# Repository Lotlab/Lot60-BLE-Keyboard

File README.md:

# Lot60-BLE Keyboard hardware

A 60% BLE/USB keyboard. License: CC-BY-SA

PLEASE REMOVE MY LOGO BEFORE SELLING THIS KEYBOARD.

## Rev A/B

Using nRF51822 as the main controller, CH554 as the USB chip.

Firmware see: [lotlab/nrf51822-keyboard](https://github.com/Lotlab/nrf51822-keyboard).

## Rev C/D/E/F

Using nRF52810 as the main controller, CH554 as the USB chip.

Firmware see:  [lotlab/nrf52-keyboard](https://github.com/Lotlab/nrf52-keyboard)

## Changelog:

### Rev B

- Fix broken ADC check pin.
- Fix ch554 powered by battery problem.

### Rev C

- Replace nRF51822 with nRF52810
- Replace USB micro with USB Type-C
- Add RGB LED.

### Rev D

- Remove UART test point.
- Change keyboard logo.
- Rework USB circuit.

### Rev E

- Rename MOSI and CLK to UART_TX and UART_RX
- Remove UART check pin.
- Swap GPIO0 and GPIO2 on the bottom jacket.
- Swap pin for GPIO2 and Caps LED.
- Add reset button for nRF52810. (Reuse with GPIO2)

### Rev F

- Add usb-powered only support.

# Lot60-BLE 键盘硬件

一个60%的蓝牙USB双模开源键盘，授权协议：CC-BY-SA。

此键盘fork自GH60，沿用GH60的键盘孔位和阵列线路。

请不要直接使用此库制作硬件并售卖。若需要售卖，请至少做出一些改动并删除LOGO。

## 版本 A/B

使用nRF51822作为键盘主控，CH552/4作为USB控制器。

键盘固件: [lotlab/nrf51822-keyboard](https://github.com/Lotlab/nrf51822-keyboard).

## 版本 C/D/E/F

使用nRF52810作为键盘主控，CH552/4作为USB控制器。

键盘固件:  [lotlab/nrf52-keyboard](https://github.com/Lotlab/nrf52-keyboard)

## 更新日志

### Rev B

- 修正电量检测ADC pin不正确的问题
- 修正CH554受到电池供电而在没有USB接入下工作的问题。

### Rev C

- 替换主控为nRF52810
- 使用Type-C接口
- 添加RGB指示灯

### Rev D

- 删除UART的测试点
- 更改键盘Logo
- 修改USB部分的线路
- 将USB下载按钮修改为正常的按钮

### Rev E

- 将MOSI和CLK重命名为UART_TX和UART_RX，并移除MISO(UART检测)PIN
- 交换了键盘底部GPIO0和GPIO2的次序
- 交换了GPIO2和大写锁定灯的硬件PIN
- 为nRF52810增加了Reset按钮（与GPIO2共用）

### Rev F

- 增加了双电源供电

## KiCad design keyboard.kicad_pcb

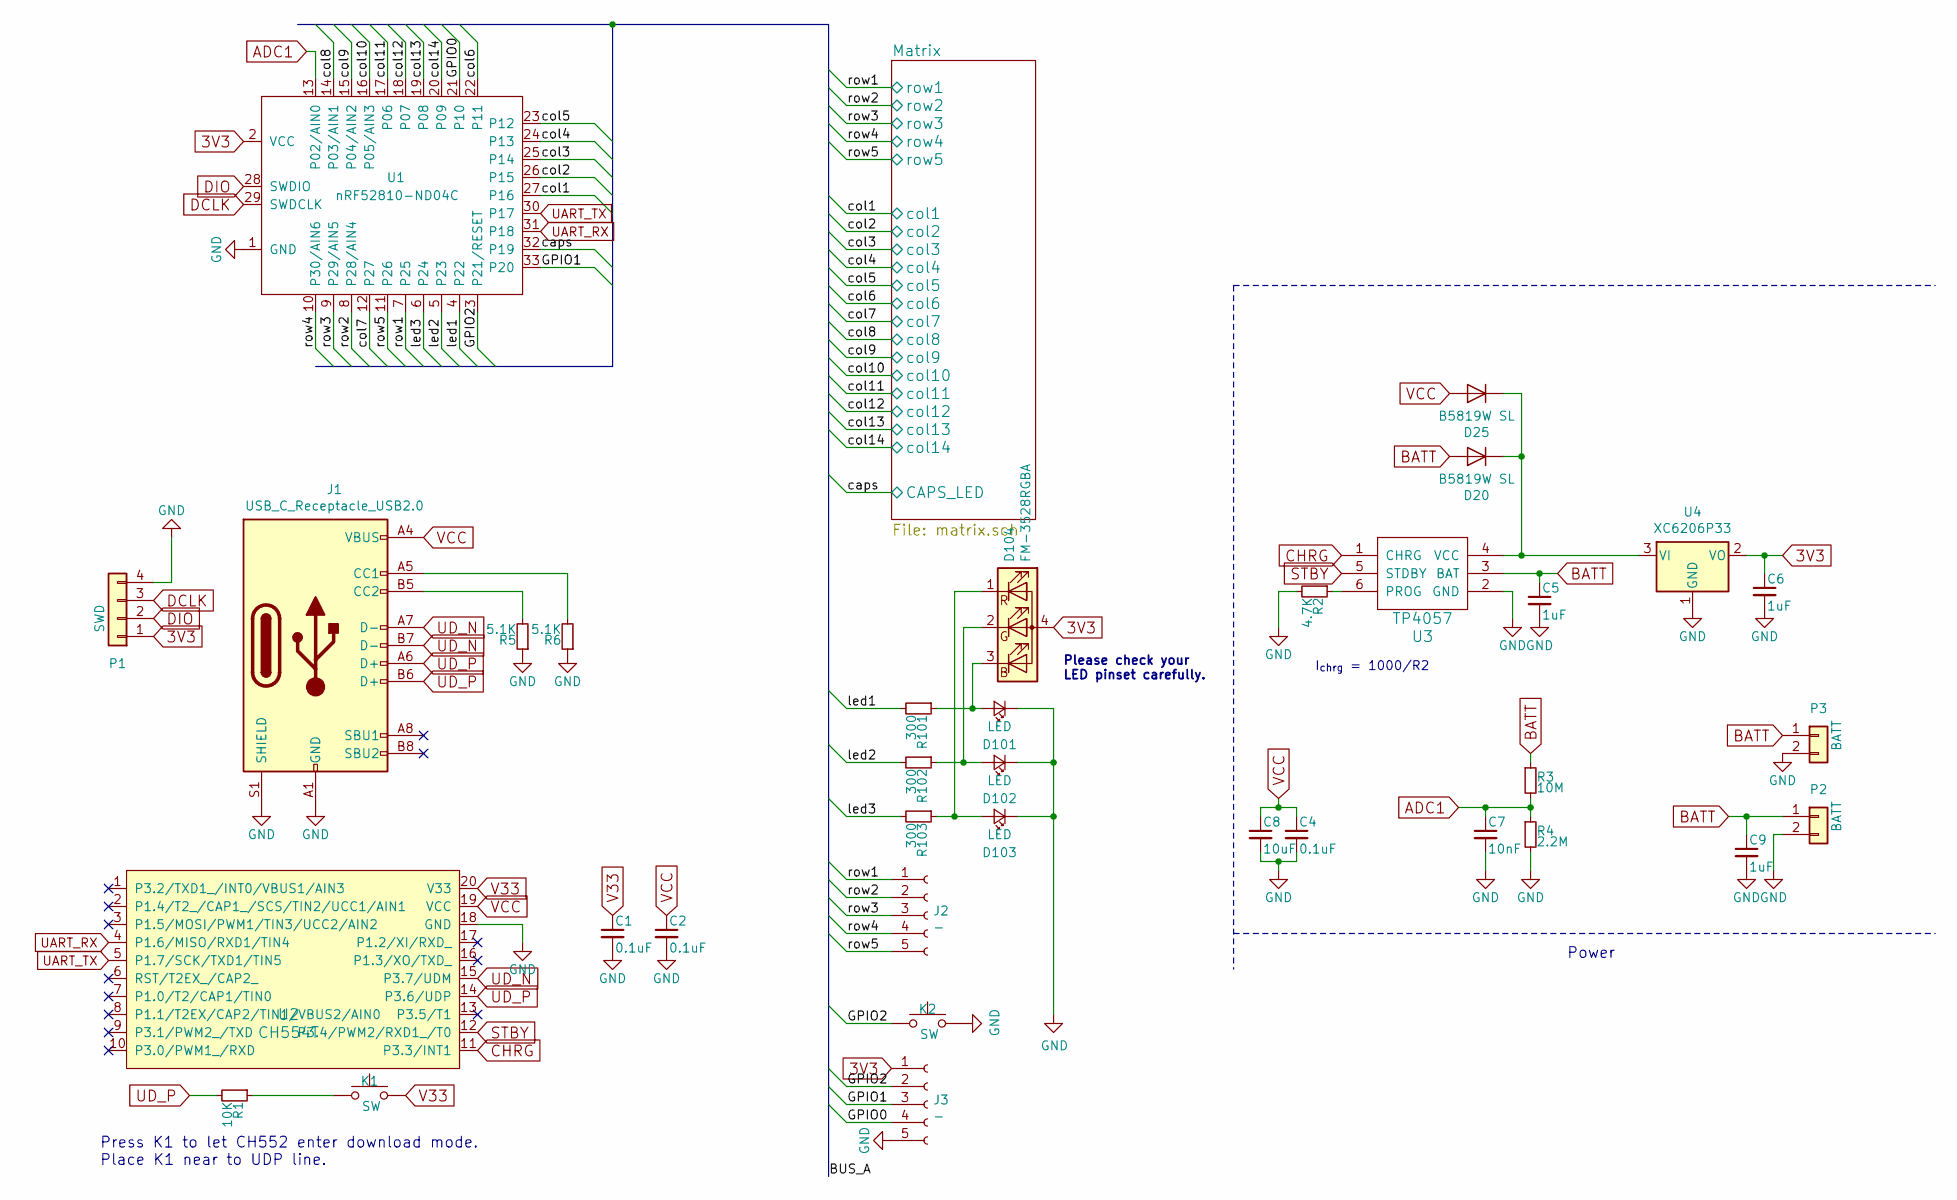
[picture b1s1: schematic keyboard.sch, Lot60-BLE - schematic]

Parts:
C1, C2, C4: 0.1uF; C_0805_2012Metric
C5, C6, C9: 1uF; C_0805_2012Metric
C7: 10nF; C_0805_2012Metric
C8: 10uF; C_0805_2012Metric
D20, D25: B5819W SL; D_SOD-123
D101, D102, D103: LED; MX1A-led
D104: FM-3528RGBA; LED_RGB_1210
J1: USB_C_Receptacle_USB2.0; USB_C_SIMPLE
J2, J3: -; PinSocket_1x05_P2.54mm_Vertical
K1, K2: SW; SW_SPST_TL3342
P1: SWD; PinSocket_1x04_P2.54mm_Vertical
P2: BATT; PinHeader_1x02_P2.54mm_Vertical
P3: BATT; PinSocket_1x02_P2.00mm_Vertical
R1: 10K; R_0805_2012Metric
R2: 4.7K; R_0805_2012Metric
R3: 10M; R_0805_2012Metric
R4: 2.2M; R_0805_2012Metric
R5, R6: 5.1K; R_0805_2012Metric
R101, R102, R103: 300; R_0805_2012Metric
U1: nRF52810-ND04C
U2: CH554T; SSOP-20_4.4x6.5mm_P0.65mm
U3: TP4057; SOT-23-6
U4: XC6206P33; SOT-23

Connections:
3V3: C6.1, D104.4 (A), J3.1, P1.1, U1.2 (VCC), U4.2 (VO)
/GPIO0: J3.4, U1.21 (P10)
/GPIO1: J3.3, U1.33 (P20)
/GPIO2: J3.2, K2.1, U1.3 (P21/RESET)
/caps: U1.32 (P19); also elsewhere on the board
/col1: U1.27 (P16); also elsewhere on the board
/col2: U1.26 (P15); also elsewhere on the board
/col3: U1.25 (P14); also elsewhere on the board
/col4: U1.24 (P13); also elsewhere on the board
/col5: U1.23 (P12); also elsewhere on the board
/col6: U1.22 (P11); also elsewhere on the board
/col7: U1.12 (P27); also elsewhere on the board
/col8: U1.14 (P03/AIN1); also elsewhere on the board
/col9: U1.15 (P04/AIN2); also elsewhere on the board
/col10: U1.16 (P05/AIN3); also elsewhere on the board
/col11: U1.17 (P06); also elsewhere on the board
/col12: U1.18 (P07); also elsewhere on the board
/col13: U1.19 (P08); also elsewhere on the board
/col14: U1.20 (P09); also elsewhere on the board
/led1: R101.2, U1.4 (P22)
/led2: R102.2, U1.5 (P23)
/led3: R103.2, U1.6 (P24)
/row1: J2.1, U1.7 (P25); also elsewhere on the board
/row2: J2.2, U1.8 (P28/AIN4); also elsewhere on the board
/row3: J2.3, U1.9 (P29/AIN5); also elsewhere on the board
/row4: J2.4, U1.10 (P30/AIN6); also elsewhere on the board
/row5: J2.5, U1.11 (P26); also elsewhere on the board
ADC1: C7.1, R3.2, R4.1, U1.13 (P02/AIN0)
BATT: C5.1, C9.1, D20.2 (A), P2.1, P3.1, R3.1, U3.3 (BAT)
CHRG: U2.11 (P3.3/INT1), U3.1 (CHRG)
DCLK: P1.3, U1.29 (SWDCLK)
DIO: P1.2, U1.28 (SWDIO)
GND: C1.2, C2.2, C4.2, C5.2, C6.2, C7.2, C8.2, C9.2, D101.1 (K), D102.1 (K), D103.1 (K), J1.A1 (GND), J1.A12 (GND), J1.B1 (GND), J1.B12 (GND), J1.S1 (SHIELD), J3.5, K2.2, P1.4, P2.2, P3.2, R2.2, R4.2, R5.1, R6.1, U1.1 (GND), U2.18 (GND), U3.2 (GND), U4.1 (GND); also elsewhere on the board
unnamed: D20.1 (K), D25.1 (K), U3.4 (VCC), U4.3 (VI)
unnamed: D101.2 (A), D104.3 (BK), R101.1
unnamed: D102.2 (A), D104.2 (GK), R102.1
unnamed: D103.2 (A), D104.1 (RK), R103.1
unnamed: J1.A5 (CC1), R6.2
unnamed: J1.B5 (CC2), R5.2
unnamed: K1.1, R1.1
unnamed: R2.1, U3.6 (PROG)
STBY: U2.12 (P3.4/PWM2/RXD1_/T0), U3.5 (STDBY)
UART_RX: U1.31 (P18), U2.4 (P1.6/MISO/RXD1/TIN4)
UART_TX: U1.30 (P17), U2.5 (P1.7/SCK/TXD1/TIN5)
UD_N: J1.A7 (D-), J1.B7 (D-), U2.15 (P3.7/UDM)
UD_P: J1.A6 (D+), J1.B6 (D+), R1.2, U2.14 (P3.6/UDP)
V33: C1.1, K1.2, U2.20 (V33)
VCC: C2.1, C4.1, C8.1, D25.2 (A), J1.A4 (VBUS), J1.A9 (VBUS), J1.B4 (VBUS), J1.B9 (VBUS), U2.19 (VCC)

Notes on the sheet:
Power
Press K1 to let CH552 enter download mode. Place K1 near to UDP line.
I_{chrg} = 1000/R2
Please check your LED pinset carefully.

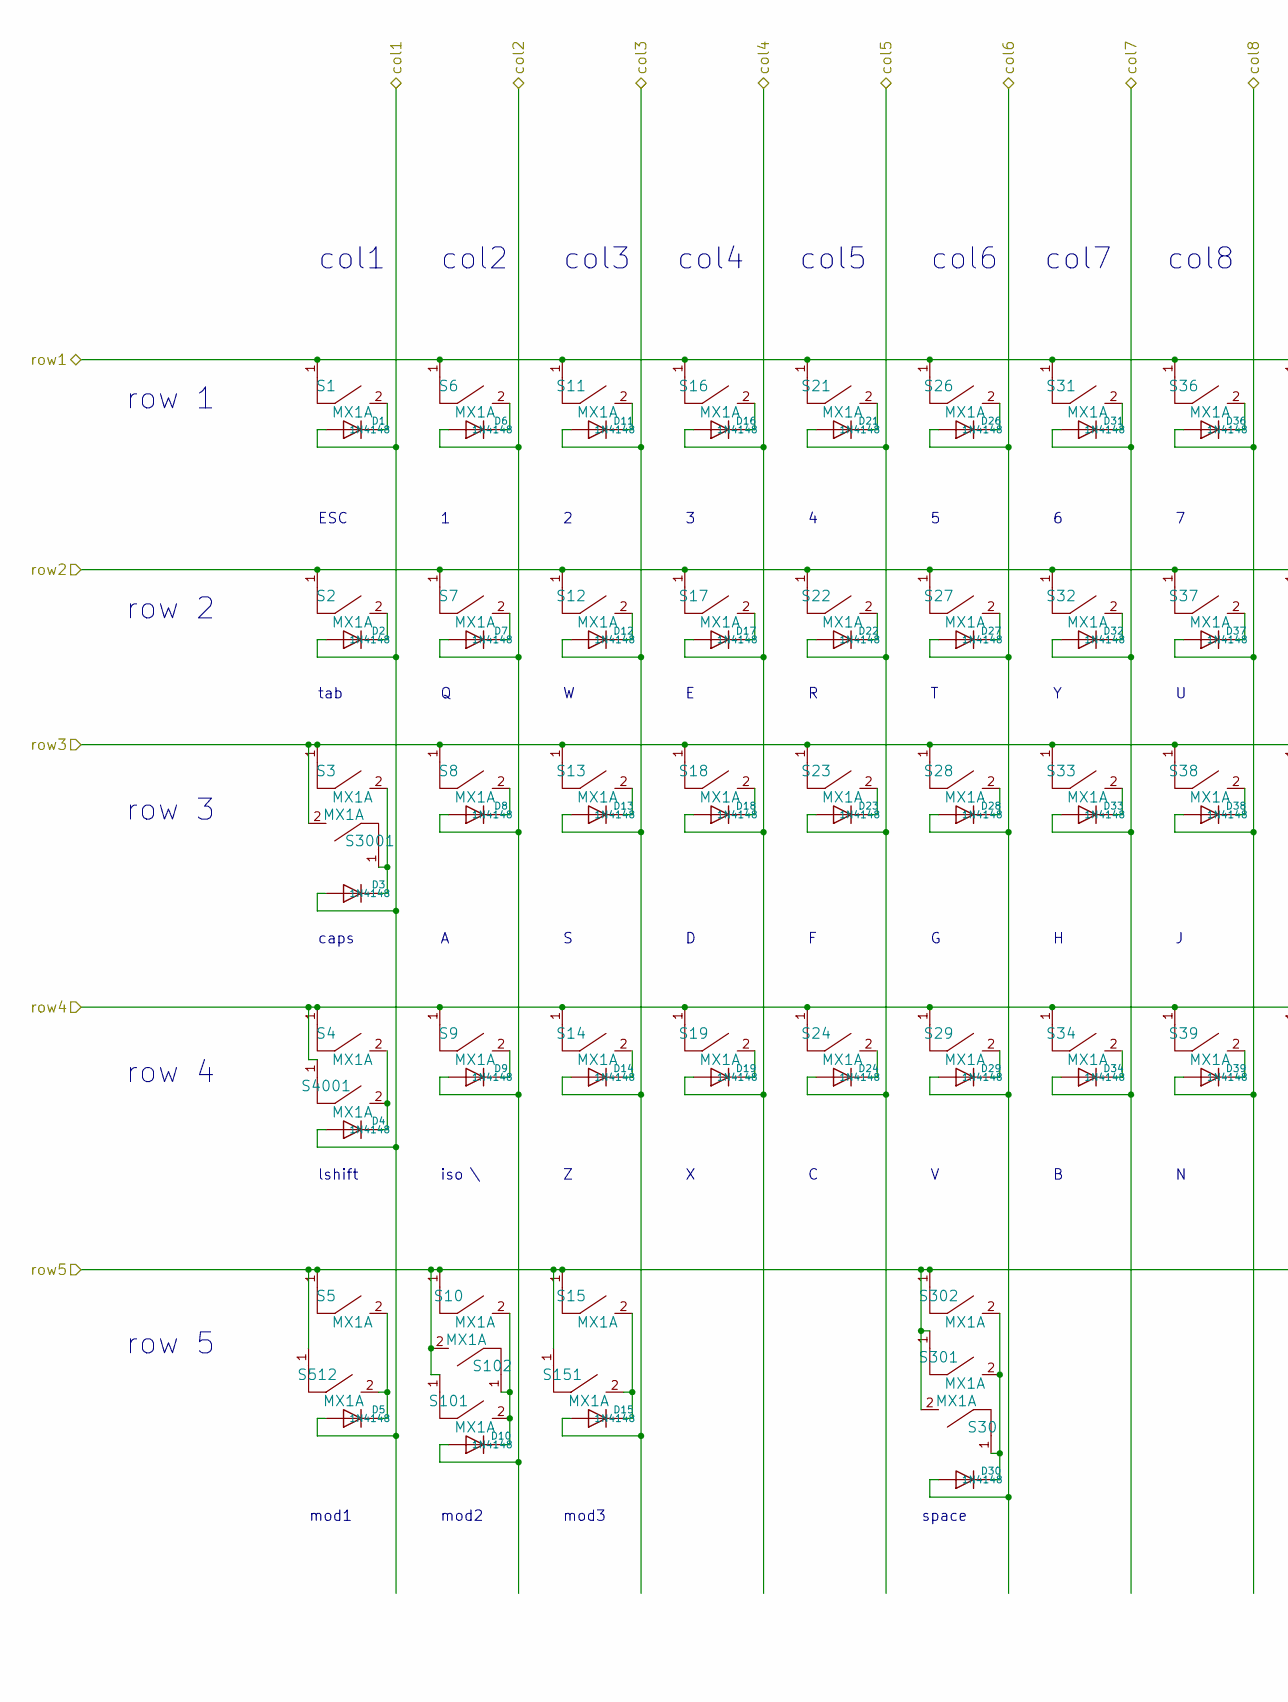
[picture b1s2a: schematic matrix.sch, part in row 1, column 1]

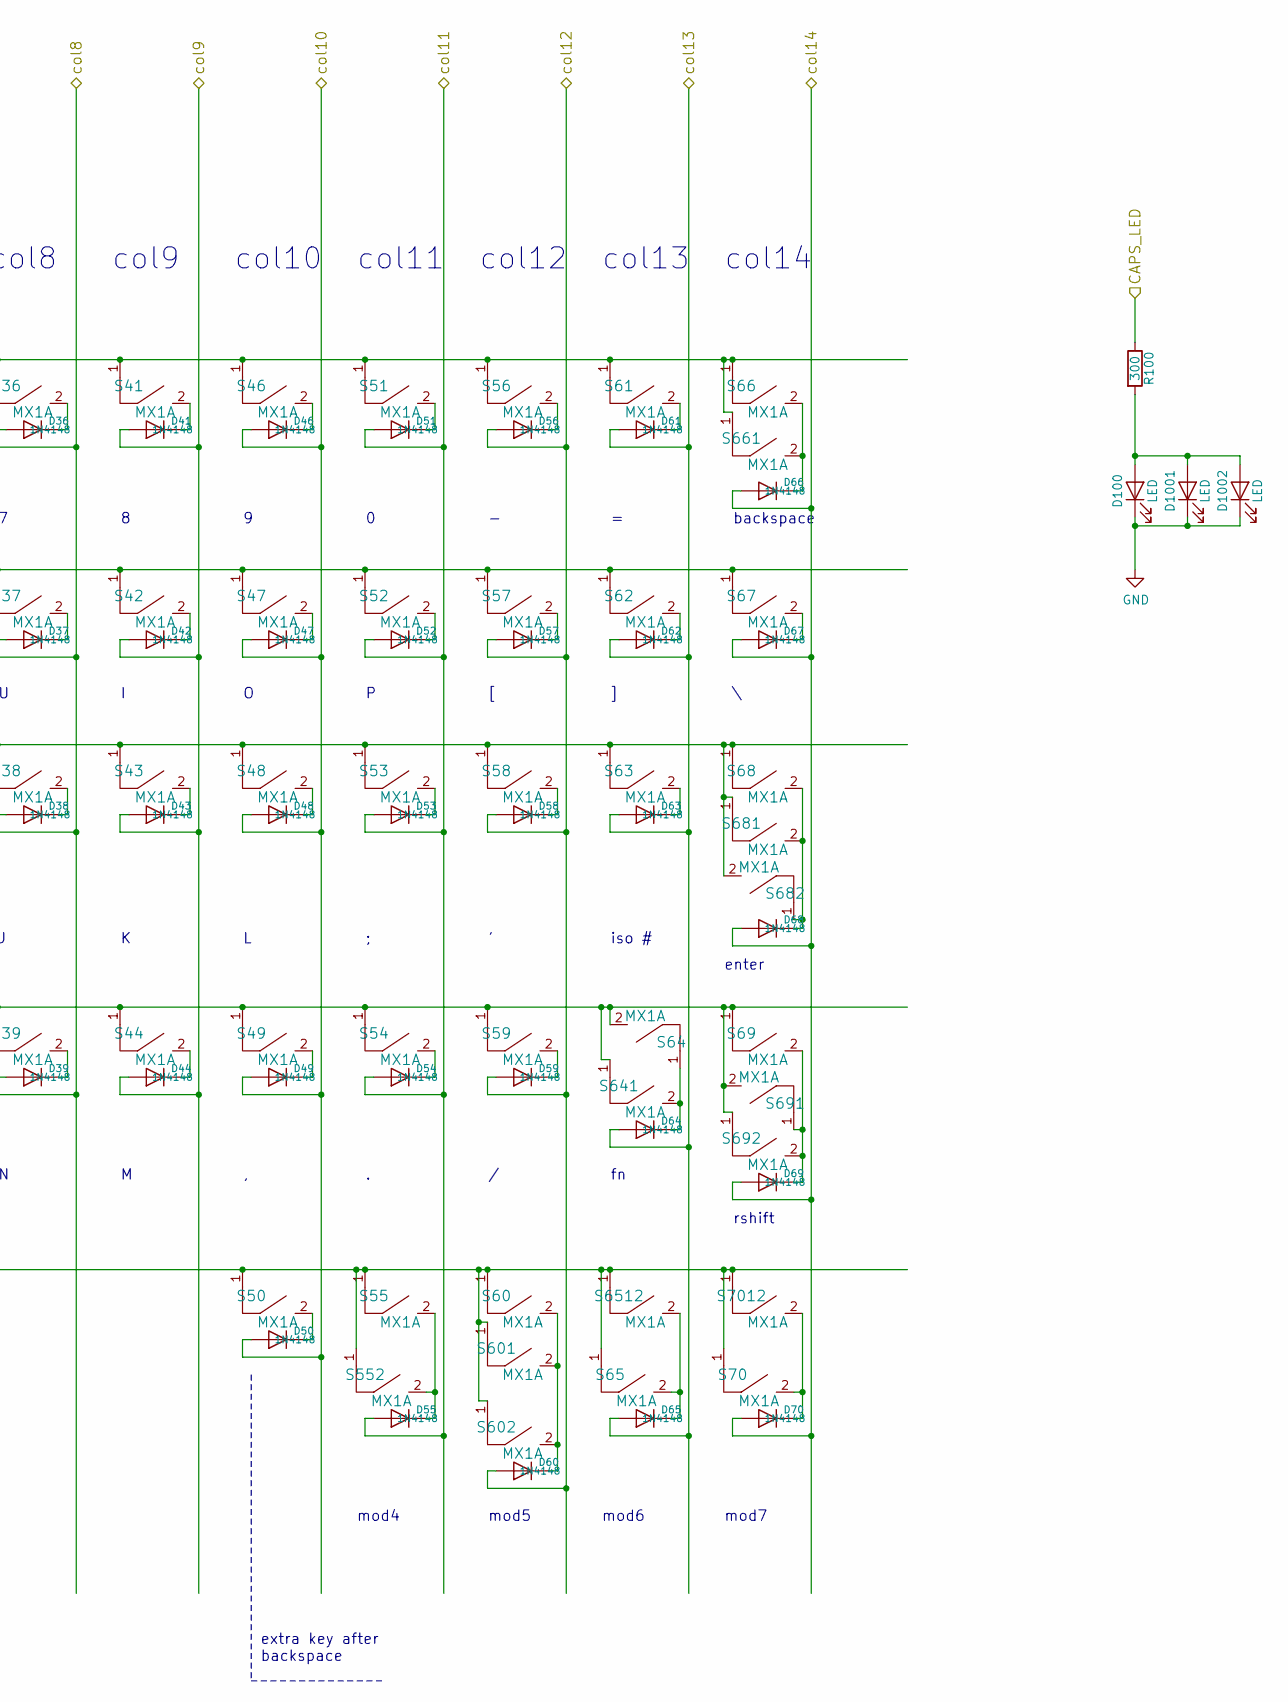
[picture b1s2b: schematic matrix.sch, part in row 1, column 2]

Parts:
D1, D2, D3, D4, D5, D6, D7, D8, D9, D10, D11, D12, D13, D14, D15, D16, D17, D18, D19, D21, D22, D23, D24, D26, D27, D28, D29, D30, D31, D32, D33, D34, D36, D37, D38, D39, D41, D42, D43, D44, D46, D47, D48, D49, D50, D51, D52, D53, D54, D55, D56, D57, D58, D59, D60, D61, D62, D63, D64, D65, D66, D67, D68, D69, D70: 1N4148; D_0805_2012Metric
D100, D1001, D1002: LED; MX1A-led
R100: 300; R_0805_2012Metric
S1, S2, S3, S4, S5, S6, S7, S8, S9, S10, S11, S12, S13, S14, S15, S16, S17, S18, S19, S21, S22, S23, S24, S26, S27, S28, S29, S30, S31, S32, S33, S34, S36, S37, S38, S39, S41, S42, S43, S44, S46, S47, S48, S49, S50, S51, S52, S53, S54, S55, S56, S57, S58, S59, S60, S61, S62, S63, S64, S65, S66, S67, S68, S69, S70, S101, S102, S151, S301, S302, S512, S552, S601, S602, S641, S661, S681, S682, S691, S692, S3001, S4001, S6512, S7012: MX1A; MX1A-simple

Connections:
/caps: R100.1; also elsewhere on the board
/col1: D1.2 (A), D2.2 (A), D3.2 (A), D4.2 (A), D5.2 (A); also elsewhere on the board
/col2: D6.2 (A), D7.2 (A), D8.2 (A), D9.2 (A), D10.2 (A); also elsewhere on the board
/col3: D11.2 (A), D12.2 (A), D13.2 (A), D14.2 (A), D15.2 (A); also elsewhere on the board
/col4: D16.2 (A), D17.2 (A), D18.2 (A), D19.2 (A); also elsewhere on the board
/col5: D21.2 (A), D22.2 (A), D23.2 (A), D24.2 (A); also elsewhere on the board
/col6: D26.2 (A), D27.2 (A), D28.2 (A), D29.2 (A), D30.2 (A); also elsewhere on the board
/col7: D31.2 (A), D32.2 (A), D33.2 (A), D34.2 (A); also elsewhere on the board
/col8: D36.2 (A), D37.2 (A), D38.2 (A), D39.2 (A); also elsewhere on the board
/col9: D41.2 (A), D42.2 (A), D43.2 (A), D44.2 (A); also elsewhere on the board
/col10: D46.2 (A), D47.2 (A), D48.2 (A), D49.2 (A), D50.2 (A); also elsewhere on the board
/col11: D51.2 (A), D52.2 (A), D53.2 (A), D54.2 (A), D55.2 (A); also elsewhere on the board
/col12: D56.2 (A), D57.2 (A), D58.2 (A), D59.2 (A), D60.2 (A); also elsewhere on the board
/col13: D61.2 (A), D62.2 (A), D63.2 (A), D64.2 (A), D65.2 (A); also elsewhere on the board
/col14: D66.2 (A), D67.2 (A), D68.2 (A), D69.2 (A), D70.2 (A); also elsewhere on the board
/row1: S1.1, S6.1, S11.1, S16.1, S21.1, S26.1, S31.1, S36.1, S41.1, S46.1, S51.1, S56.1, S61.1, S66.1, S661.1; also elsewhere on the board
/row2: S2.1, S7.1, S12.1, S17.1, S22.1, S27.1, S32.1, S37.1, S42.1, S47.1, S52.1, S57.1, S62.1, S67.1; also elsewhere on the board
/row3: S3.1, S8.1, S13.1, S18.1, S23.1, S28.1, S33.1, S38.1, S43.1, S48.1, S53.1, S58.1, S63.1, S68.1, S681.1, S682.2, S3001.2; also elsewhere on the board
/row4: S4.1, S9.1, S14.1, S19.1, S24.1, S29.1, S34.1, S39.1, S44.1, S49.1, S54.1, S59.1, S64.2, S69.1, S641.1, S691.2, S692.1, S4001.1; also elsewhere on the board
/row5: S5.1, S10.1, S15.1, S30.2, S50.1, S55.1, S60.1, S65.1, S70.1, S101.1, S102.2, S151.1, S301.1, S302.1, S512.1, S552.1, S601.1, S602.1, S6512.1, S7012.1; also elsewhere on the board
GND: D100.1 (K), D1001.1 (K), D1002.1 (K); also elsewhere on the board
unnamed: D1.1 (K), S1.2
unnamed: D2.1 (K), S2.2
unnamed: D3.1 (K), S3.2, S3001.1
unnamed: D4.1 (K), S4.2, S4001.2
unnamed: D5.1 (K), S5.2, S512.2
unnamed: D6.1 (K), S6.2
unnamed: D7.1 (K), S7.2
unnamed: D8.1 (K), S8.2
unnamed: D9.1 (K), S9.2
unnamed: D10.1 (K), S10.2, S101.2, S102.1
unnamed: D11.1 (K), S11.2
unnamed: D12.1 (K), S12.2
unnamed: D13.1 (K), S13.2
unnamed: D14.1 (K), S14.2
unnamed: D15.1 (K), S15.2, S151.2
unnamed: D16.1 (K), S16.2
unnamed: D17.1 (K), S17.2
unnamed: D18.1 (K), S18.2
unnamed: D19.1 (K), S19.2
unnamed: D21.1 (K), S21.2
unnamed: D22.1 (K), S22.2
unnamed: D23.1 (K), S23.2
unnamed: D24.1 (K), S24.2
unnamed: D26.1 (K), S26.2
unnamed: D27.1 (K), S27.2
unnamed: D28.1 (K), S28.2
unnamed: D29.1 (K), S29.2
unnamed: D30.1 (K), S30.1, S301.2, S302.2
unnamed: D31.1 (K), S31.2
unnamed: D32.1 (K), S32.2
unnamed: D33.1 (K), S33.2
unnamed: D34.1 (K), S34.2
unnamed: D36.1 (K), S36.2
unnamed: D37.1 (K), S37.2
unnamed: D38.1 (K), S38.2
unnamed: D39.1 (K), S39.2
unnamed: D41.1 (K), S41.2
unnamed: D42.1 (K), S42.2
unnamed: D43.1 (K), S43.2
unnamed: D44.1 (K), S44.2
unnamed: D46.1 (K), S46.2
unnamed: D47.1 (K), S47.2
unnamed: D48.1 (K), S48.2
unnamed: D49.1 (K), S49.2
unnamed: D50.1 (K), S50.2
unnamed: D51.1 (K), S51.2
unnamed: D52.1 (K), S52.2
unnamed: D53.1 (K), S53.2
unnamed: D54.1 (K), S54.2
unnamed: D55.1 (K), S55.2, S552.2
unnamed: D56.1 (K), S56.2
unnamed: D57.1 (K), S57.2
unnamed: D58.1 (K), S58.2
unnamed: D59.1 (K), S59.2
unnamed: D60.1 (K), S60.2, S601.2, S602.2
unnamed: D61.1 (K), S61.2
unnamed: D62.1 (K), S62.2
unnamed: D63.1 (K), S63.2
unnamed: D64.1 (K), S64.1, S641.2
unnamed: D65.1 (K), S65.2, S6512.2
unnamed: D66.1 (K), S66.2, S661.2
unnamed: D67.1 (K), S67.2
unnamed: D68.1 (K), S68.2, S681.2, S682.1
unnamed: D69.1 (K), S69.2, S691.1, S692.2
unnamed: D70.1 (K), S70.2, S7012.2
unnamed: D100.2 (A), D1001.2 (A), D1002.2 (A), R100.2

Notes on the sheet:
row 1
row 2
row 3
row 4
row 5
col1
col2
col3
col4
col5
col6
col7
col9
col10
col11
col12
col13
col14
col8
ESC
backspace
tab
caps
iso #
enter
lshift
iso \
rshift
mod1
mod2
mod3
space
mod4
mod5
mod6
mod7
extra key after backspace

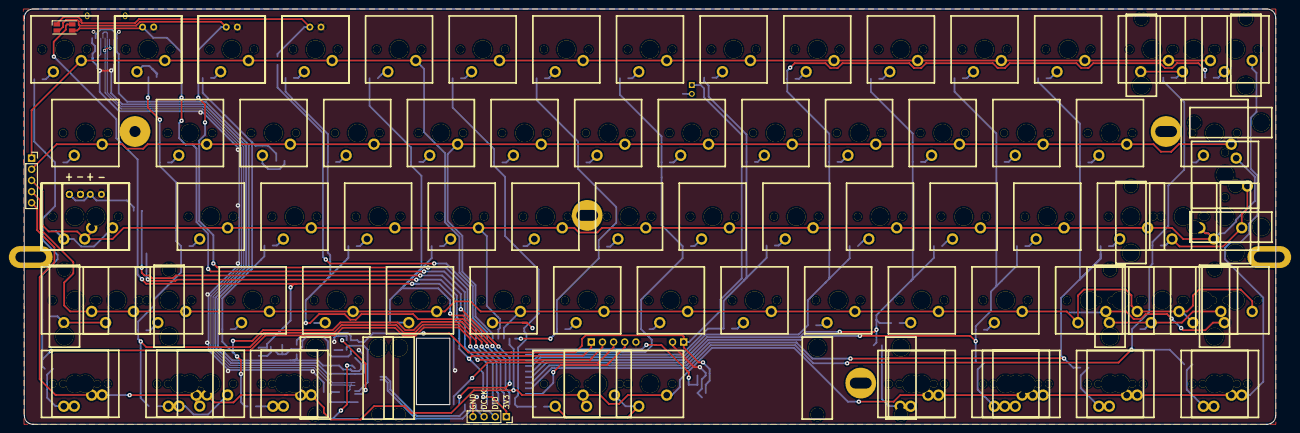
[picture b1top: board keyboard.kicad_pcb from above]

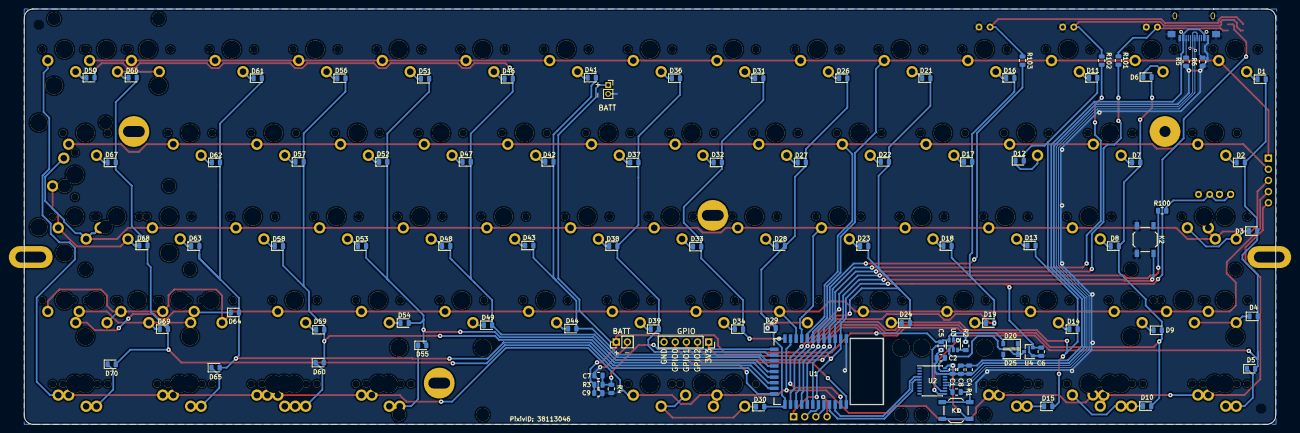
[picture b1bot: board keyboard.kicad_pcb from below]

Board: 2 copper layers, 285.0 x 94.6 mm, 209 parts (95 on the bottom side), 114 nets.

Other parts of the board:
HOLE, HOLE2: VAL**; PKRHSL
HOLE1: VAL**; PKRH
HOLE3: VAL**; PKRHC
HOLE#2: VAL**; PKRH
MXLED: VAL**; PKRH
MXST1, MXST2, MXST3, MXST4, MXST5, MXST6, MXST7, MXST8, MXST9, MXST10, MXST11, MXST12, MXST13, MXST14, MXST15: VAL**; MXST

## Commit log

2018-02-21 initial commitment
2018-02-22 细节修正
2018-04-22 元件丢正面
2018-05-21 修正几个问题
    修正ADC接口不正确的问题
    增加防反冲二极管
2019-01-23 应该是改了些布线方面的问题
2019-01-23 add README.md
2019-03-21 替换接口为Type-C
2019-04-03 使用52810替换51822
2019-04-03 微调布线
2019-04-18 更换type-c接口的封装
2019-04-23 增加电容，更改type-c封装为非沉板式
2019-04-24 增加RGB LED
2019-05-16 添加一些文字说明
2019-05-16 更新README
2019-05-31 修改USB部分的部分线路布局
2019-05-31 remove rescue file
2019-06-13 add LICENSE
2019-06-13 change pcb logo
2019-08-15 Rev.E
2019-08-15 修改Readme，修正丝印不正确的问题
2019-09-01 增加顶部电池P2.0接口，修改LED为RGBA封装，避免优信店内LED需要反装的问题。微调LOGO位置
2019-09-01 将SS14封装更换为更易买到的SMA，将XC6206P30换为更易买到的XC6206P33
2019-09-01 更新部分cache的库
2019-09-06 为蓝牙模块天线位置添加开孔，修改GPIO接口位置
2019-09-06 增加使用的自定义封装库
2019-09-09 修正阵列二极管在原理图上的方向与封装方向不一致的问题
2019-11-05 移动二极管位置以增强外壳兼容性
2019-11-20 改进了空格和左GUI键的接线顺序，使其更难粘连
2019-11-20 改进供电部分，现在支持仅USB供电了
2019-11-25 移除多余的导线

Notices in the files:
keyboard.kicad_pcb:
©2018 Lotlab
©2018-2019
